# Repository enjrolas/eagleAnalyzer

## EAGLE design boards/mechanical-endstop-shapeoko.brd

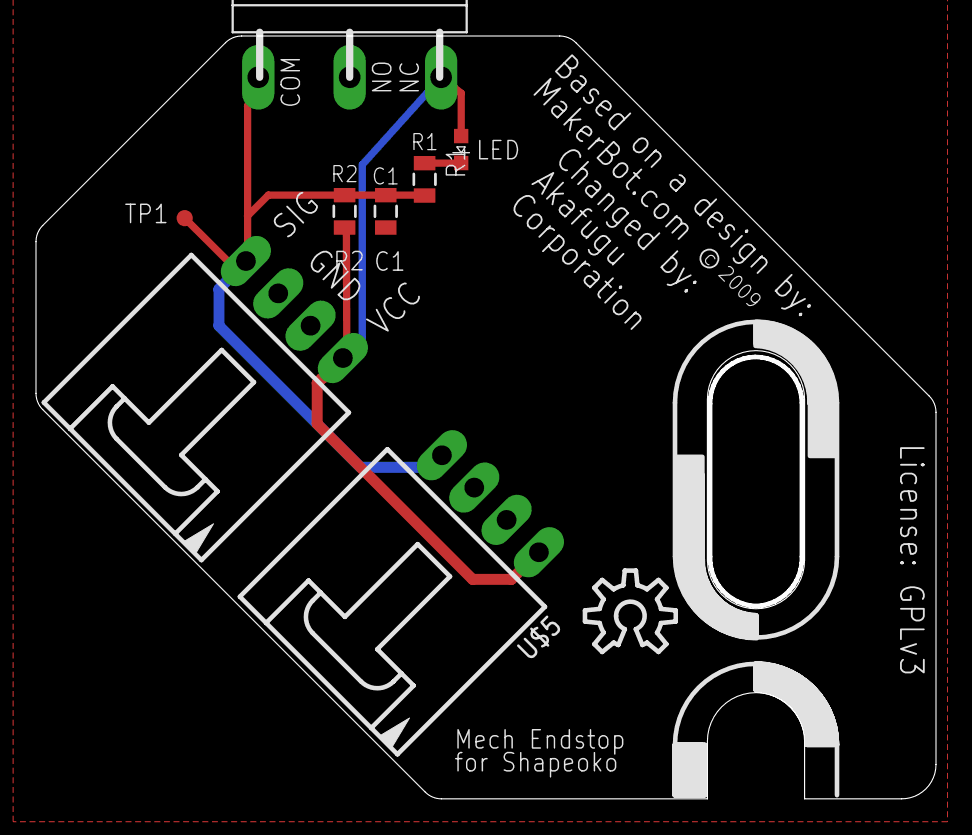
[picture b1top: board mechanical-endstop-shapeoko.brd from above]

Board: 2 copper layers, 50.0 x 42.4 mm, 9 parts (0 on the bottom side), 4 nets.

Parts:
C1: 0.1uF; 0805-CAP
DETECT: LED-0603
R1: 1K; R0805
R2: 10K; R0805
TP1: PTR1TP09R; TP09R
U$1, U$5: CDROM-HOR; 70553-04
U$2: OMRON-D2FA; OMRON-D2F-A
U$4: OSHW-LOGO-OUTLINE

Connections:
GND: C1.2, U$1.2, U$1.3, U$2.NO, U$5.2, U$5.3
unnamed: DETECT.C, R1.2
unnamed: C1.1, R1.1, R2.1, TP1.TP, U$1.4, U$2.COM, U$5.4
VCC: DETECT.A, R2.2, U$1.1, U$2.NC, U$5.1

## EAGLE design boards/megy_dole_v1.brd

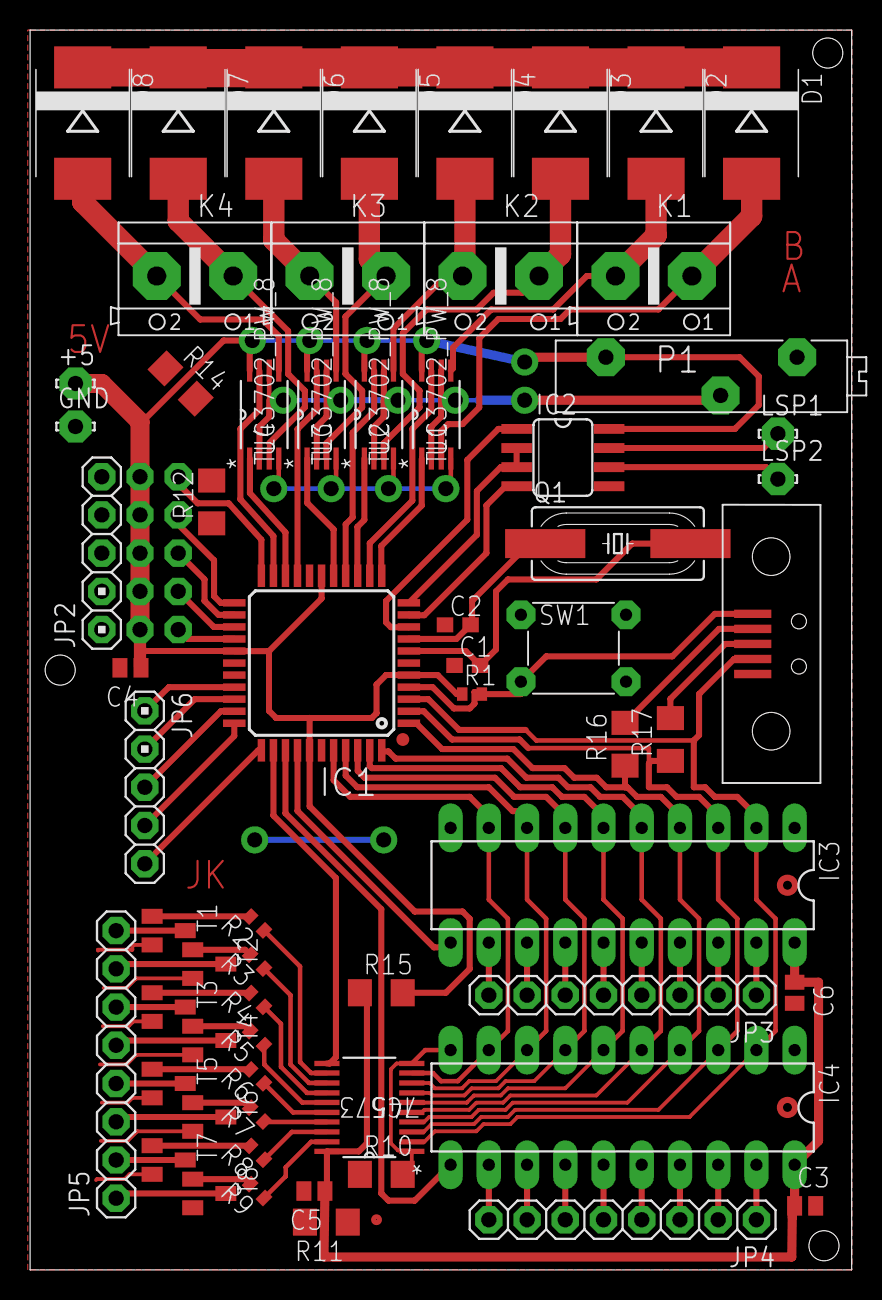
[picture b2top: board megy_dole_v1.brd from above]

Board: 2 copper layers, 54.6 x 82.4 mm, 65 parts (1 on the bottom side), 90 nets.

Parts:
+5: LSP10
C1, C2: C0603
C3, C4, C5, C6: 100n; C0504
D1: ES3D; SMC
D2, D3, D4, D5, D6, D7, D8: SMC
GND: LSP10
IC1: MEGA16-A; TQFP44
IC2: MAX485csa+; SO08
IC3, IC4: 74AC573N; DIL20
IC5: 74573; PW20
JP1: 2X05
JP2, JP6: 1X05
JP3, JP4, JP5: 1X08
K1, K2, K3, K4: ARK500/2
LSP1, LSP2: LSP10
P1: 10K; PM19
Q1: HC49UP
R1: 4K7; R0402
R2, R3, R4, R5, R6, R7, R8, R9: 220R; R0402
R10, R11, R12, R14, R15, R16, R17: R1206
SW1: P-B1720
T1, T2, T3, T4, T5, T6, T7, T8: BSS138; SOT23
U1, U2, U3, U4: TLC3702_PW_8; PW8
U$1: SEI-5

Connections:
GND: C1.1, C2.1, C3.2, C4.2, C5.2, C6.2, D1.C, D2.C, D3.C, D4.C, D5.C, D6.C, D7.C, D8.C, GND.MP, IC1.6, IC1.18, IC1.28, IC1.39, IC2.5, IC3.1, IC3.10, IC4.1, IC4.10, IC5.1, IC5.10, JP2.1, JP2.2, JP2.3, JP2.4, JP2.5, P1.B, R10.1, R10.2, R11.1, R11.2, R12.1, R12.2, R14.1, R14.2, SW1.2, T1.2, T2.2, T3.2, T4.2, T5.2, T6.2, T7.2, T8.2, U1.4, U2.4, U3.4, U4.4, U$1.P$5
MISO: IC1.2, IC3.3, IC4.3, IC5.3, R17.1
MOSI: IC1.1, IC3.4, IC4.4, IC5.4, R16.1
unnamed: IC1.10, IC2.4
unnamed: IC1.11, IC2.2, IC2.3
unnamed: IC2.7, LSP1.MP
unnamed: IC1.9, IC2.1
unnamed: IC1.37, IC3.11
unnamed: IC2.6, LSP2.MP
unnamed: C1.2, IC1.7, Q1.2
unnamed: C2.2, IC1.8, Q1.1
unnamed: IC1.26, JP1.9
unnamed: IC1.25, JP1.7
unnamed: IC1.24, JP1.5
unnamed: IC1.23, JP1.3
unnamed: IC1.22, JP1.1
unnamed: IC1.40, IC3.9, IC4.9, IC5.9
unnamed: IC1.41, IC3.8, IC4.8, IC5.8
unnamed: IC1.42, IC3.7, IC4.7, IC5.7
unnamed: IC1.12, U1.1
unnamed: IC1.13, U1.7
unnamed: IC1.20, U4.1
unnamed: D1.A, K1.1, U1.3
unnamed: D2.A, K1.2, U1.5
unnamed: IC1.43, IC3.6, IC4.6, IC5.6
unnamed: IC1.44, IC3.5, IC4.5, IC5.5
unnamed: IC1.21, U4.7
unnamed: D7.A, K4.1, U4.3
unnamed: D8.A, K4.2, U4.5
unnamed: P1.C, U1.2, U1.6, U2.2, U2.6, U3.2, U3.6, U4.2, U4.6
unnamed: IC1.14, U2.1
unnamed: IC1.15, U2.7
unnamed: D3.A, K2.1, U2.3
unnamed: D4.A, K2.2, U2.5
unnamed: IC1.16, U3.1
unnamed: IC1.19, U3.7
unnamed: D5.A, K3.1, U3.3
unnamed: D6.A, K3.2, U3.5
unnamed: R16.2, U$1.P$2
unnamed: R17.2, U$1.P$3
unnamed: IC4.19, JP4.1
unnamed: IC4.18, JP4.2
unnamed: IC4.17, JP4.3
unnamed: IC4.16, JP4.4
unnamed: IC3.19, JP3.1
unnamed: IC3.18, JP3.2
unnamed: IC3.17, JP3.3
unnamed: IC3.16, JP3.4
unnamed: IC3.15, JP3.5
unnamed: IC3.14, JP3.6
unnamed: IC3.13, JP3.7
unnamed: IC3.12, JP3.8
unnamed: IC4.15, JP4.5
unnamed: IC4.14, JP4.6
unnamed: IC4.13, JP4.7
unnamed: IC4.12, JP4.8
unnamed: IC1.36, IC4.11
unnamed: IC1.35, IC5.11
unnamed: IC5.12, R2.1
unnamed: R2.2, T1.1
unnamed: JP5.8, T1.3
unnamed: R3.2, T2.1
unnamed: IC5.13, R3.1
unnamed: JP5.7, T2.3
unnamed: IC5.19, R9.1
unnamed: R4.2, T3.1
unnamed: IC5.14, R4.1
unnamed: JP5.6, T3.3
unnamed: R5.2, T4.1
unnamed: R6.2, T5.1
unnamed: R7.2, T6.1
unnamed: R8.2, T7.1
unnamed: R9.2, T8.1
unnamed: JP5.5, T4.3
unnamed: JP5.4, T5.3
unnamed: JP5.3, T6.3
unnamed: JP5.2, T7.3
unnamed: JP5.1, T8.3
unnamed: IC5.18, R8.1
unnamed: IC5.17, R7.1
unnamed: IC5.16, R6.1
unnamed: IC5.15, R5.1
unnamed: IC1.30, JP6.1
unnamed: IC1.31, JP6.2
unnamed: IC1.32, JP6.3
unnamed: IC1.33, JP6.4
unnamed: IC1.34, JP6.5
RESET: IC1.4, R1.2, SW1.1, U$1.P$1
SCK: IC1.3, IC3.2, IC4.2, IC5.2, U$1.P$4
VCC: +5.MP, C3.1, C4.1, C5.1, C6.1, IC1.5, IC1.17, IC1.27, IC1.38, IC2.8, IC3.20, IC4.20, IC5.20, JP1.2, JP1.4, JP1.6, JP1.8, JP1.10, P1.A, R1.1, R15.1, R15.2, U1.8, U2.8, U3.8, U4.8

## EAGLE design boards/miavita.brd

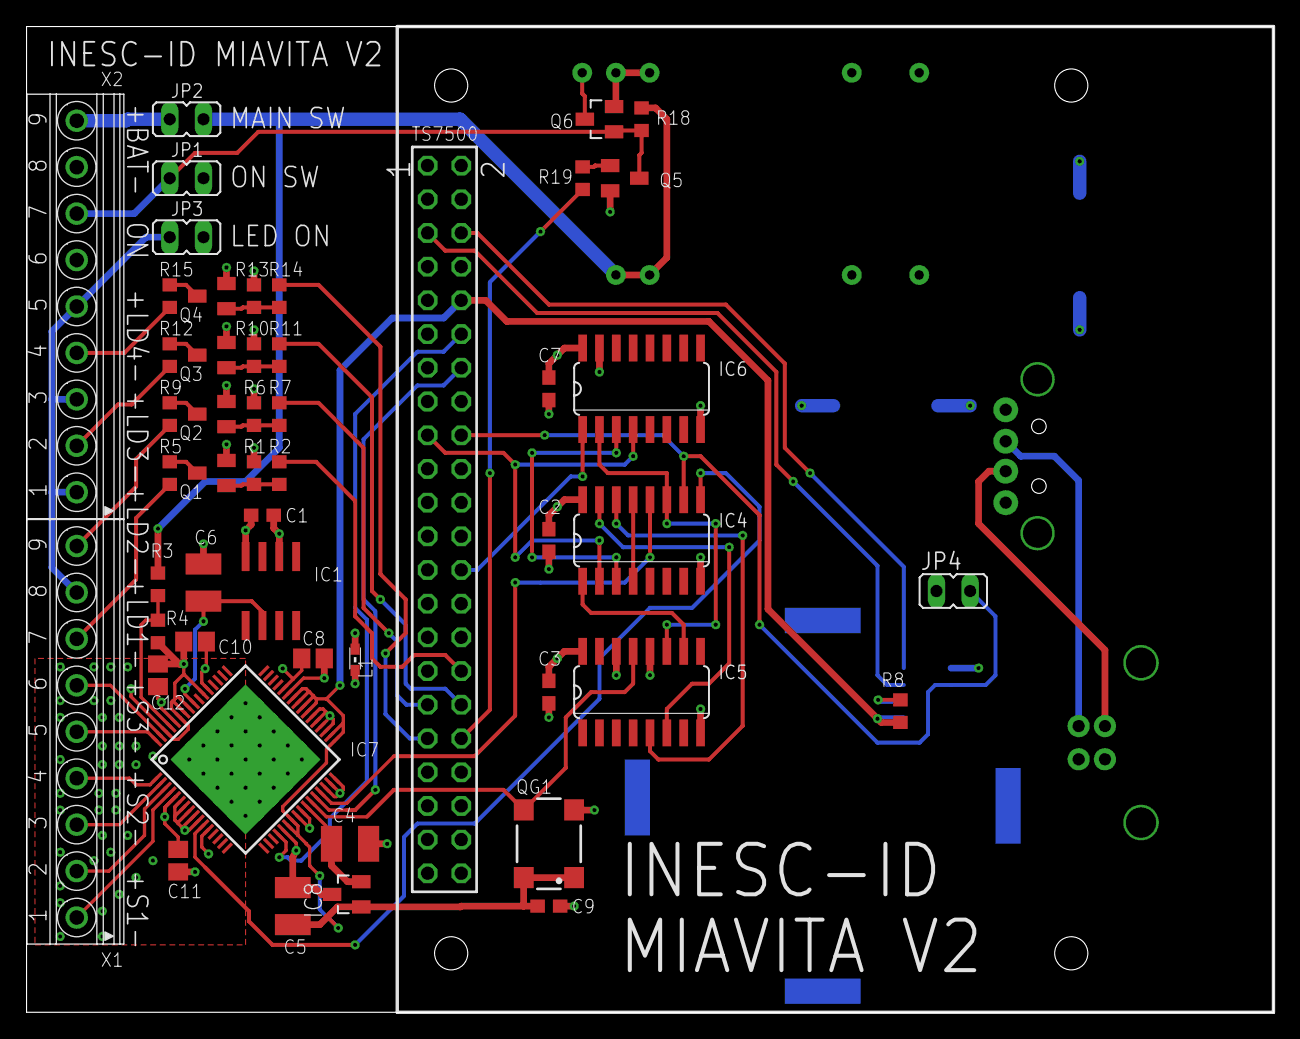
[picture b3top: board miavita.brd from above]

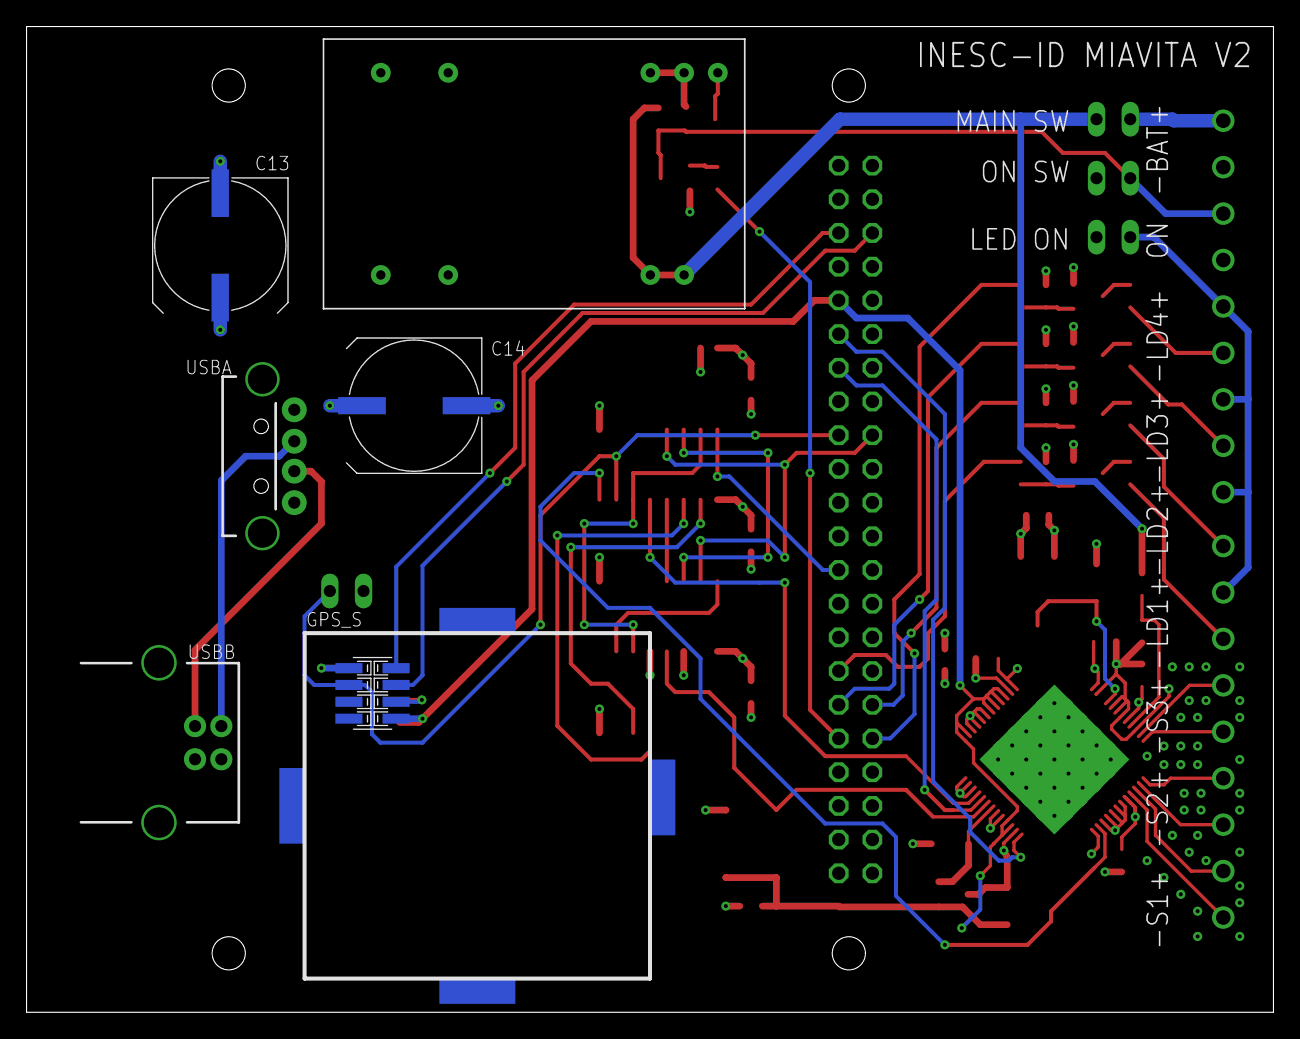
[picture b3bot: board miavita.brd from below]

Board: 4 copper layers, 94.0 x 74.3 mm, 56 parts (6 on the bottom side), 55 nets.

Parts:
C1: 1uF; C0603
C2, C3, C7: 100nF; C0603
C4, C5, C6: 10uF; C1210
C8, C10, C11, C12: 10uF; C0805
C9: 0.1uF; C0603
C13, C14: 220uF/35V; UD-10X10_NICHICON
GPS_S: 1296-T08; 1296-08
IC1: REF02D; SO08
IC4: 4572D; SO16
IC5: 74AC590D; SO16
IC6: 74LS157D; SO16
IC7: ADS1278; HTQFP-64-PAP
IC8: R3318AI; SOT23
JP1, JP2, JP3, JP4: JP1
L1: L0603
Q1, Q2, Q3, Q4, Q5: BC847B; SOT23
Q6: 2N7002CK; SOT23
QG1: SM77H
R1, R6, R10, R13, R18: 47K; R0603
R2, R7, R11, R14, R19: 10K; R0603
R3: 510k; R0603
R4, R8: 100k; R0603
R5, R9, R12, R15: 220R; R0603
TS7500: SSW-122-02-S-D
U1: TEN 8-1211; TRACOPOWER_TEN-8-SERIES
USBA: USB-A-H
USBB: USBPTH; USB-B-PTH
X1, X2: 1751316

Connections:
2.5V: C6.1, IC1.6, IC7.56
+1V8: C4.1, IC7.26, IC8.2
+3V3: C5.1, C9.1, GPS_S.8, IC7.22, IC7.23, IC7.33, IC7.34, IC7.39, IC7.40, IC7.41, IC7.42, IC8.1, QG1.1, QG1.4, R8.1, TS7500.10
+5V: C1.1, C2.1, C3.1, C7.1, C13.+, C14.+, IC1.2, IC4.16, IC5.16, IC6.16, JP3.2, L1.2, TS7500.15, U1.14, USBA.GND, X2.6
+12V: JP2.2, R3.2, R18.1, U1.22, U1.23
ADC_DATA: IC7.20, TS7500.12
CONT_144: IC4.3, IC6.3
CONT_RST: IC4.1, IC5.10
DR_INT: IC4.2, IC6.4, TS7500.17
FIRST_ADC_INT: IC4.11, IC5.11, IC6.2
GND: C1.2, C2.2, C3.2, C4.2, C5.2, C6.2, C7.2, C8.2, C9.2, C10.2, C11.2, C12.2, C13.-, C14.-, GPS_S.1, IC1.4, IC4.8, IC5.8, IC5.12, IC5.14, IC6.8, IC6.15, IC7.6, IC7.7, IC7.8, IC7.9, IC7.10, IC7.12, IC7.21, IC7.24, IC7.25, IC7.30, IC7.31, IC7.32, IC7.35, IC7.36, IC7.37, IC7.38, IC7.43, IC7.54, IC7.57, IC7.58, IC7.59, IC7.62, IC7.EXP1, IC7.EXP2, IC7.EXP3, IC7.EXP4, IC7.EXP5, IC7.EXP6, IC7.EXP7, IC7.EXP8, IC7.EXP9, IC7.EXP10, IC7.EXP11, IC7.EXP12, IC7.EXP13, IC7.EXP14, IC7.EXP15, IC7.EXP16, IC7.EXP17, IC7.EXP18, IC7.EXP19, IC7.EXP20, IC7.EXP21, IC7.EXP22, IC7.EXP23, IC7.EXP24, IC7.EXP25, IC8.3, JP1.1, JP4.1, Q1.2, Q2.2, Q3.2, Q4.2, Q5.2, Q6.2, QG1.2, R1.2, R4.2, R6.2, R10.2, R13.2, TS7500.7, TS7500.16, U1.2, U1.3, U1.16, USBA.VBUS, USBB.GND, X2.8
GPS_PPS: GPS_S.3, IC4.10, JP4.2, TS7500.18
LED1: R2.1, TS7500.32
LED2: R7.1, TS7500.33
LED3: R11.1, TS7500.34
LED4: R14.1, TS7500.35
unnamed: IC6.1, TS7500.26
unnamed: IC4.15, IC5.6
unnamed: IC4.14, IC5.5
unnamed: IC4.9, IC7.11
unnamed: IC4.4, IC4.13
unnamed: IC4.12, IC7.29
unnamed: IC7.3, X1.2
unnamed: Q5.1, R19.2
unnamed: IC7.4, X1.1
unnamed: IC7.1, X1.4
unnamed: IC7.61, R3.1, R4.1
unnamed: USBA.D+, USBB.D-
unnamed: IC7.63, X1.6
unnamed: Q2.1, R6.1, R7.2
unnamed: Q2.3, R9.1
unnamed: IC5.13, IC7.27, QG1.3
unnamed: USBA.D-, USBB.D+
unnamed: C8.1, C10.1, C11.1, C12.1, IC7.5, IC7.44, IC7.53, IC7.60, L1.1
unnamed: R9.2, X1.9
unnamed: Q3.1, R10.1, R11.2
unnamed: Q3.3, R12.1
unnamed: R12.2, X2.2
unnamed: Q4.1, R13.1, R14.2
unnamed: Q4.3, R15.1
unnamed: R15.2, X2.4
unnamed: JP2.1, X2.9
unnamed: JP3.1, X1.8, X2.1, X2.3, X2.5
unnamed: IC7.2, X1.3
unnamed: JP1.2, Q5.3, Q6.1, R18.2, X2.7
unnamed: Q6.3, U1.1
unnamed: IC7.64, X1.5
unnamed: Q1.3, R5.1
unnamed: Q1.1, R1.1, R2.2
unnamed: R5.2, X1.7
unnamed: GPS_S.2, TS7500.6
unnamed: GPS_S.4, TS7500.5
unnamed: GPS_S.6, R8.2
ON: R19.1, TS7500.36
SPI_CLOCK: IC7.28, TS7500.14

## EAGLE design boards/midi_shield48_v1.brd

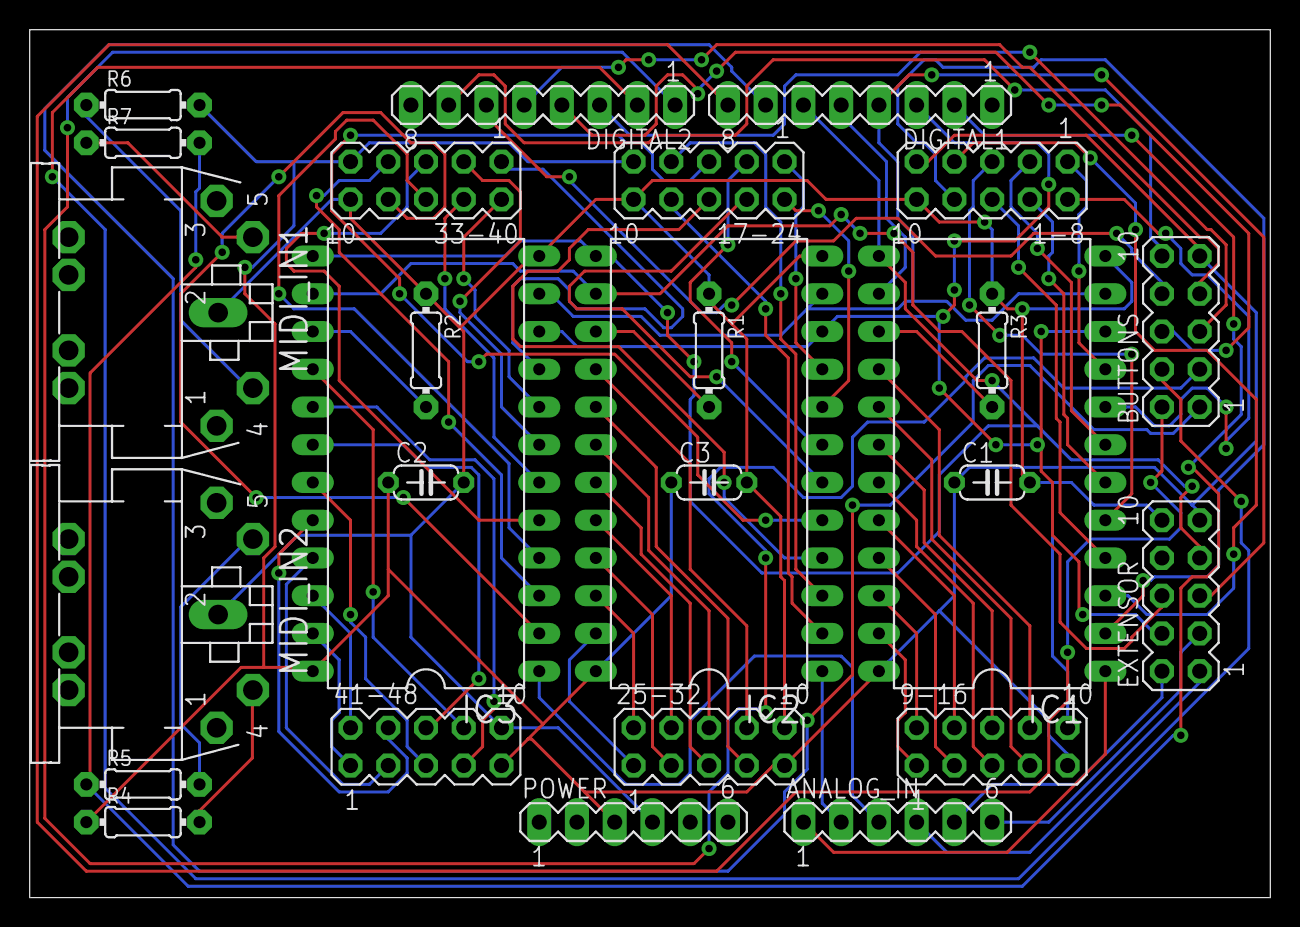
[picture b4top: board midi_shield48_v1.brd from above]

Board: 2 copper layers, 83.5 x 58.4 mm, 27 parts (0 on the bottom side), 77 nets.

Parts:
1-8, 9-16, 17-24, 25-32, 33-40, 41-48: MA05-2
ANALOG_IN: MA06-1
BUTTONS: MA05-2
C1, C2, C3: 0.1uF; C050-024X044
DIGITAL1, DIGITAL2: MA08-1
EXTENSOR: MA05-2
IC1, IC2, IC3: 4067N; DIL24-6
MIDI_IN1, MIDI_IN2: MIDIJACK; CP-2350
POWER: MA06-1
R1, R2, R3: 10k; 0204/7
R4, R5, R6, R7: 220; 0204/7

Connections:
ACOMM1: ANALOG_IN.1, IC1.1
ACOMM2: ANALOG_IN.2, IC2.1
ACOMM3: ANALOG_IN.3, IC3.1
ACOMM4: ANALOG_IN.4, EXTENSOR.1
ACOMM5: ANALOG_IN.5, EXTENSOR.2
ACOMM6: ANALOG_IN.6, EXTENSOR.3
BUTTON1: BUTTONS.1, DIGITAL1.7
BUTTON2: BUTTONS.2, DIGITAL1.8
BUTTON3: BUTTONS.3, DIGITAL2.1
BUTTON4: BUTTONS.4, DIGITAL2.2
DIGITAL_GND: BUTTONS.10, DIGITAL2.7
GND: 1-8.10, 9-16.10, 17-24.10, 25-32.10, 33-40.10, 41-48.10, C1.2, C2.2, C3.2, EXTENSOR.10, IC1.12, IC2.12, IC3.12, MIDI_IN1.2, MIDI_IN2.2, POWER.4, R1.1, R2.1, R3.1
LED1: BUTTONS.5, DIGITAL2.3
LED2: BUTTONS.6, DIGITAL2.4
LED3: BUTTONS.7, DIGITAL2.5
LED4: BUTTONS.8, DIGITAL2.6
M1P1: 1-8.1, IC1.9
M1P2: 1-8.2, IC1.8
M1P3: 1-8.3, IC1.7
M1P4: 1-8.4, IC1.6
M1P5: 1-8.5, IC1.5
M1P6: 1-8.6, IC1.4
M1P7: 1-8.7, IC1.3
M1P8: 1-8.8, IC1.2
M1P9: 9-16.1, IC1.23
M1P10: 9-16.2, IC1.22
M1P11: 9-16.3, IC1.21
M1P12: 9-16.4, IC1.20
M1P13: 9-16.5, IC1.19
M1P14: 9-16.6, IC1.18
M1P15: 9-16.7, IC1.17
M1P16: 9-16.8, IC1.16
M2P1: 17-24.1, IC2.9
M2P2: 17-24.2, IC2.8
M2P3: 17-24.3, IC2.7
M2P4: 17-24.4, IC2.6
M2P5: 17-24.5, IC2.5
M2P6: 17-24.6, IC2.4
M2P7: 17-24.7, IC2.3
M2P8: 17-24.8, IC2.2
M2P9: 25-32.1, IC2.23
M2P10: 25-32.2, IC2.22
M2P11: 25-32.3, IC2.21
M2P12: 25-32.4, IC2.20
M2P13: 25-32.5, IC2.19
M2P14: 25-32.6, IC2.18
M2P15: 25-32.7, IC2.17
M2P16: 25-32.8, IC2.16
M3P1: 33-40.1, IC3.9
M3P2: 33-40.2, IC3.8
M3P3: 33-40.3, IC3.7
M3P4: 33-40.4, IC3.6
M3P5: 33-40.5, IC3.5
M3P6: 33-40.6, IC3.4
M3P7: 33-40.7, IC3.3
M3P8: 33-40.8, IC3.2
M3P9: 41-48.1, IC3.23
M3P10: 41-48.2, IC3.22
M3P11: 41-48.3, IC3.21
M3P12: 41-48.4, IC3.20
M3P13: 41-48.5, IC3.19
M3P14: 41-48.6, IC3.18
M3P15: 41-48.7, IC3.17
M3P16: 41-48.8, IC3.16
MIDITX: DIGITAL1.2, R5.1, R7.2
unnamed: IC1.15, R3.2
unnamed: IC2.15, R1.2
unnamed: IC3.15, R2.2
unnamed: MIDI_IN2.5, R5.2
unnamed: MIDI_IN2.4, R4.2
unnamed: MIDI_IN1.5, R7.1
unnamed: MIDI_IN1.4, R6.1
S0: DIGITAL1.3, EXTENSOR.4, IC1.10, IC2.10, IC3.10
S1: DIGITAL1.4, EXTENSOR.5, IC1.11, IC2.11, IC3.11
S2: DIGITAL1.5, EXTENSOR.6, IC1.14, IC2.14, IC3.14
S3: DIGITAL1.6, EXTENSOR.7, IC1.13, IC2.13, IC3.13
VCC: 1-8.9, 9-16.9, 17-24.9, 25-32.9, 33-40.9, 41-48.9, BUTTONS.9, C1.1, C2.1, C3.1, EXTENSOR.9, IC1.24, IC2.24, IC3.24, POWER.3, R4.1, R6.2

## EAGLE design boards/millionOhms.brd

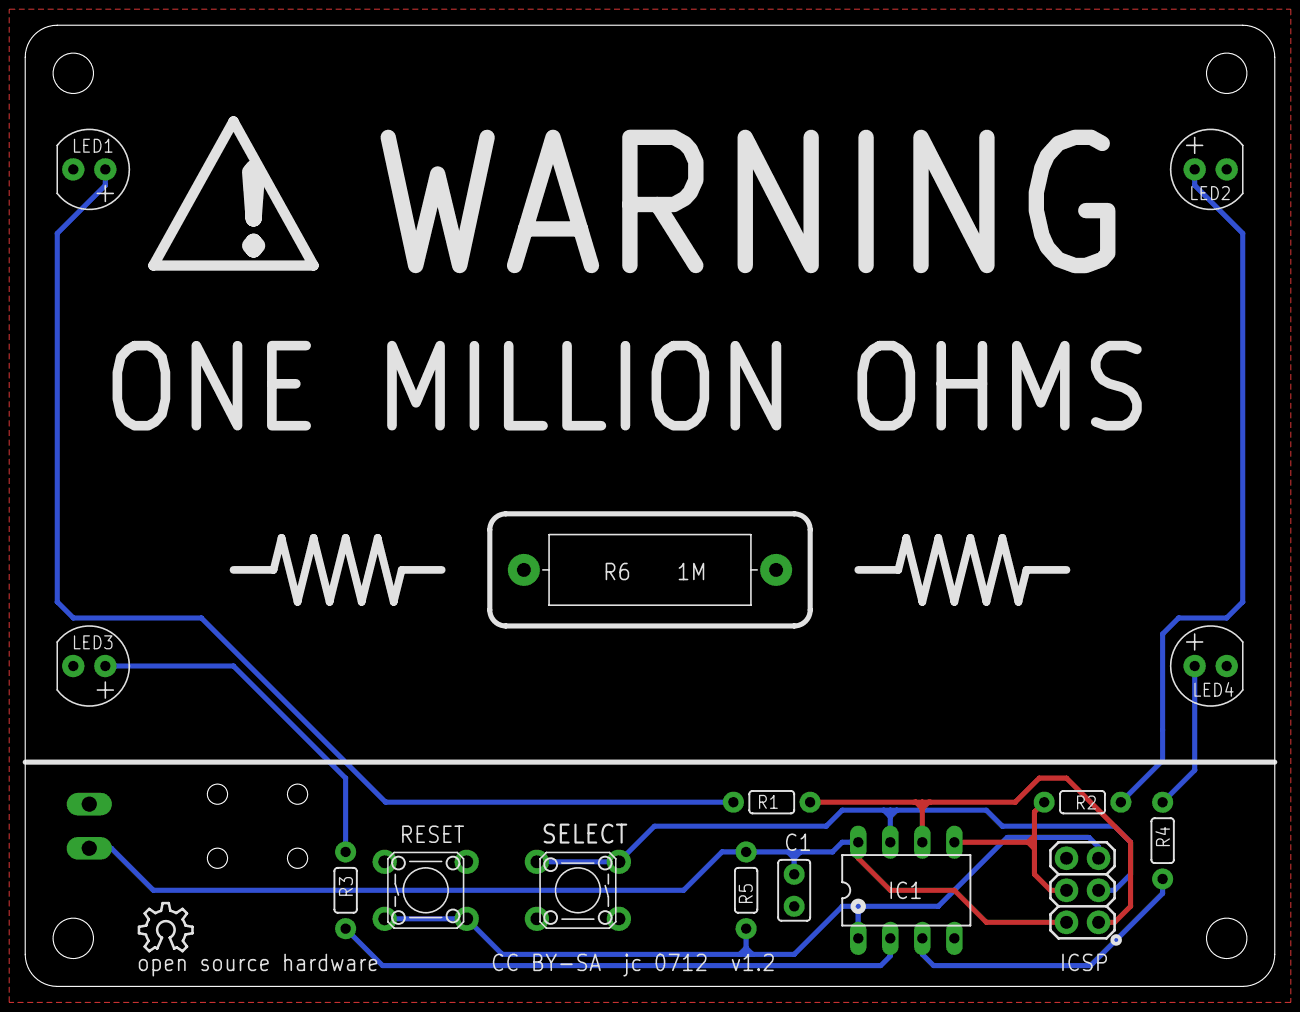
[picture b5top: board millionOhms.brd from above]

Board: 2 copper layers, 99.1 x 76.2 mm, 17 parts (1 on the bottom side), 12 nets.

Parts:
C1: 2.2uF; C025-025X050
IC1: ATtiny85V-10PU; DIL08
J1: ICSP; 2X3
LED1, LED2, LED3, LED4: 5mm; LED5MM
LOGO2: OSHW_LOGO_8MILX0150-NT; OSHW_8X150_NOTEXT
R1, R2, R3, R4: 100; 0204/6
R5: 10K; 0204/6
R6: 1M; 5616/20
S1: SELECT; B3F-10XXOCT
S2: RESET; B3F-10XXOCT
TB1: +3VDC-; OST-TB-2-3.5MM

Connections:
GND: C1.2, IC1.4, J1.6, LED1.K, LED2.K, LED3.K, LED4.K, S1.1, S1.2, S2.1, S2.2, TB1.P$2
MISO: IC1.6, J1.1, R1.2
MOSI: IC1.5, J1.4, R2.2
unnamed: LED2.A, R2.1
unnamed: LED1.A, R1.1
unnamed: LED3.A, R3.1
unnamed: LED4.A, R4.1
unnamed: IC1.2, R3.2
unnamed: IC1.3, R4.2
RESET: IC1.1, J1.5, R5.1, S2.3, S2.4
SCK: IC1.7, J1.3, S1.3, S1.4
VCC: C1.1, IC1.8, J1.2, R5.2, TB1.P$1

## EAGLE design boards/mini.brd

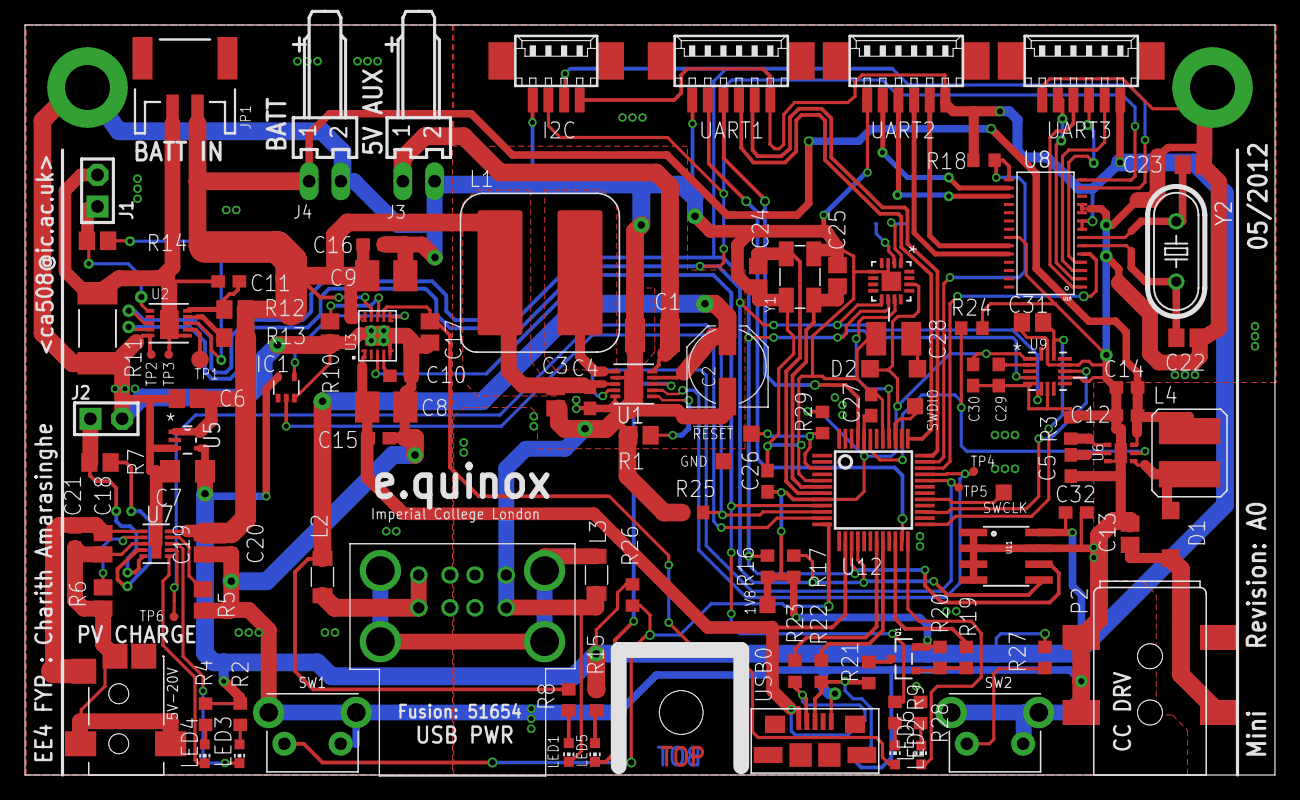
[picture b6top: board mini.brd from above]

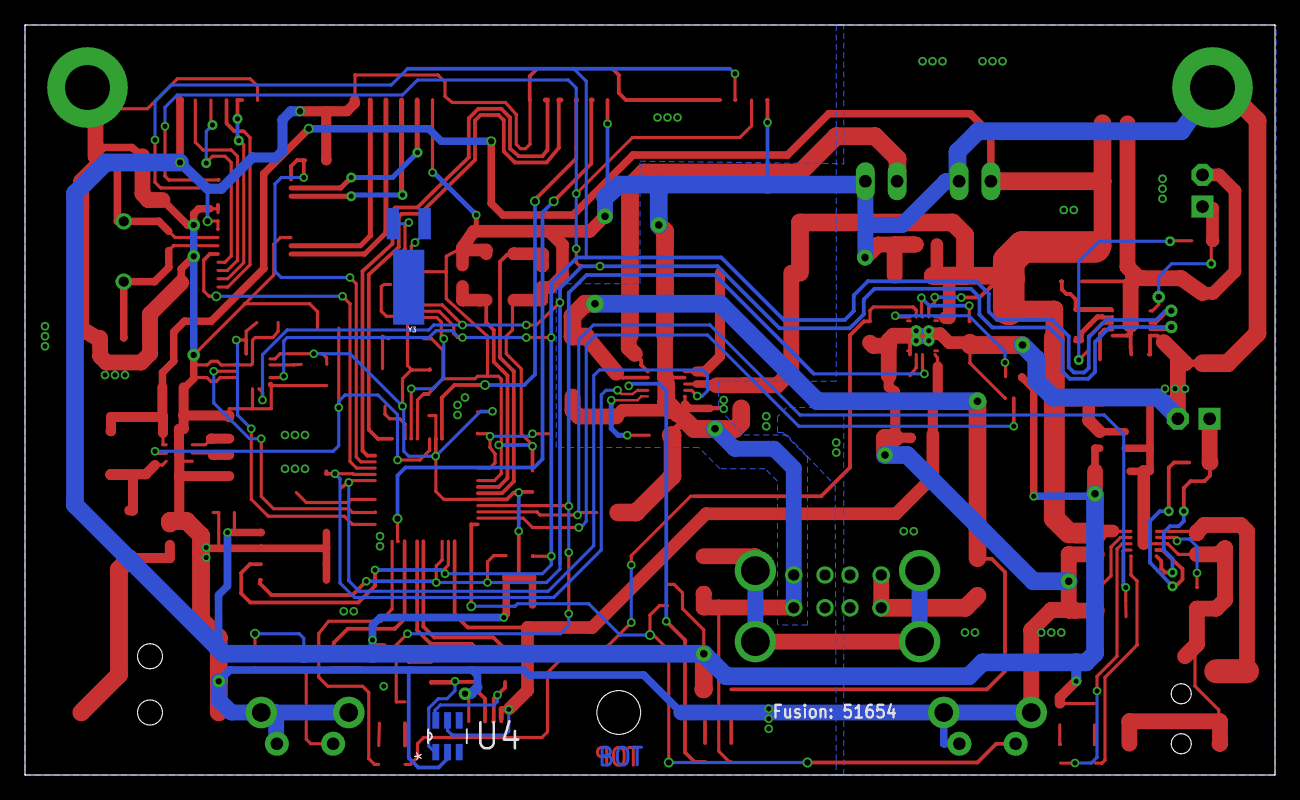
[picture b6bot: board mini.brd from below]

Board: 2 copper layers, 100.0 x 60.0 mm, 116 parts (2 on the bottom side), 84 nets.

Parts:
1V8: TPSTP13SQ; TP13SQ
!RESET!: TPSTP13SQ; TP13SQ
C1: 22uF; C1210
C2: 150uF; PANASONIC_D
C3: 10uF; C0805
C4, C14, C29, C30, C32: 0.1uF; C0603
C5: 220nF; C0603
C6: 100nF; C0805
C7: 1uF; C1206
C8, C9: 10uF; B/3528-21R
C10: 1n; C0603
C11: 10n; C0603
C12: 1uF; C0603
C13, C17, C18, C19: 1uF; C0805
C15, C16, C20, C21, C26, C27: 100n; C0603
C22, C23, C24, C25: C0805
C28: 0.015F; C3225
C31: 4.7uF; C0805
D1: MBR0540T1; SOD123
D2: SOD123
GND: TPSTP13SQ; TP13SQ
I2C: 53261-04
IC1: 74LVC1G06DCK; SC70-5
J1, J2: F-1X02-SIP-100-40; SIP-100-02-40
J3, J4: 22-05-7028-02; 7395-02
JP1: JST-2-SMD
L1: 2.2uH; SDR1006
L2, L3: 30ohm; L3216C
L4: 22uH; VLCF-SERIES
LED1: USB_ON; CHIP-LED0603
LED2: USB_CHG_GD; CHIP-LED0603
LED3: CHG; CHIP-LED0603
LED4: PG; CHIP-LED0603
LED5: USB_FAULT; CHIP-LED0603
LED6: USRLED; CHIP-LED0603
P1: CLIFF_DCJACK1.3MM; FC68145S
P2: CLIFF_DCJACK2.1-2.5MM; FC6814XS
Q1: MMBT2907; SOT23-R
R1: 28.7k; R0805
R2, R4, R15: 100; R0603
R3: 2.7; R0603
R5: RDPM; R0805
R6: 800; R0805
R7: RVTSB; R0805
R8: 1K; R0603
R9: 200; R0603
R10: 80k; R0805
R11: 0.015; R2512
R12: 150; R0805
R13: 1K; R0805
R14: 10K; R0805
R16, R17, R24, R26, R27, R29: 2.7k; R0603
R18: 1.5k; R0603
R19: 2K; R0603
R20, R25: 10K; R0603
R21: 1.5K; R0603
R22, R23: 33; R0603
R28: 500; R0603
SW1, SW2: B3F-3152; B3F-315X
SWCLK: TPSTP13SQ; TP13SQ
SWDIO: TPSTP13SQ; TP13SQ
TP1: TPTP14R; TP14R
TP2, TP3, TP4, TP5, TP6: TPTP07R; TP07R
U1: TPS2500; SON50P300X300X100-11N
U2: DS2786G+; DFN300X300X80-11N
U3: ISL9203; INTERSIL_DFN_3X3
U4: IP4220CZ6; SOT95P275X110-6N
U5: NCP4588DSQ25T1G; SOT65P210X110-5N
U6: TPS61160ADRVT; SON65P210X210X80-7N
U7: BQ24210DQCT; SON50P200X300X80-11N
U8: M41T62Q6F; QFN50P300X300X100-17N
U9: MMA8453Q; QFN50P300X300X100-16N
U10: SC16IS752; TSSOP28
U11: EEPROM-I2CSMD; SO08
U12: LPC11U24FBD48/401; LQFP48
UART1, UART2, UART3: 53261-06
USB0: TE1981584-1; TE-MICROUSB-AB
USB2: MULTICOMP-MC32594; MC32594
Y1: TXC-7B
Y2: 1.8432M; HC49U-V
Y3: 32.768kHz; CRYSTAL-32KHZ-SMD

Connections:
1.8V: 1V8.TP, C7.1, C26.1, C27.1, C30.1, C32.1, D2.A, I2C.1, IC1.5, Q1.2, R2.2, R4.2, R15.2, R16.2, R17.2, R18.2, R20.2, R26.2, R27.2, R29.2, U5.4, U8.14, U9.1, U10.8, U10.9, U11.8, U12.8, U12.44, UART1.1, UART2.1, UART3.1
!CHRG_ST!: R9.1, U3.P3, U12.9
!EN_PVCHG!: R25.2, TP6.TP, U7.7, U12.10
!EXT_UART_RST!: U10.5, U12.34
!USB_CHG_EN!: IC1.2, U12.11
+5V: C8.+, C15.1, U3.P1, U4.5, U12.14, USB0.P1
+5V/1: C2.+, L2.2, R8.2, U1.9
+5V/2: C1.1, J3.1, U1.10
+12V: C13.1, D1.C, P2.3
+18V: C18.1, C21.1, P1.3, U7.1
AXM_INT: U9.11, U12.27
AXM_ON: C31.1, U9.14, U12.25
CHRG_EN: IC1.4, U3.P6
EN_5V: TP5.TP, U1.4, U12.32
EN_USB: TP4.TP, U1.7, U12.33
EXT_UART_IRQ: R18.1, U10.15, U12.35
FG_AIN0: J1.1, R14.1, U2.1
FG_VOUT: R14.2, U2.8
GND: C1.2, C2.-, C3.1, C4.2, C5.2, C6.2, C7.2, C8.-, C9.-, C10.2, C12.2, C13.2, C14.2, C15.2, C16.2, C17.2, C18.2, C19.2, C20.2, C21.2, C22.1, C23.1, C24.1, C25.1, C26.2, C27.2, C28.2, C29.2, C30.2, C31.2, C32.2, GND.TP, I2C.4, IC1.3, J2.2, J3.2, J4.2, L3.2, LED1.C, P1.1, P1.4A, P1.4B, P2.1A, P2.1B, R1.1, R3.1, R5.1, R6.1, R10.1, R11.2, R24.1, R25.1, R28.1, SW1.2, SW1.3, SW1.4, SW2.2, SW2.3, SW2.4, TP2.TP, U1.2, U1.5, U1.11, U2.5, U3.P5, U3.P$1, U3.P$2, U3.P$3, U3.P$4, U3.PAD, U4.2, U5.3, U6.3, U6.7, U7.3, U7.11, U8.3, U8.5, U8.17, U9.5, U9.7, U9.10, U9.12, U9.15, U10.10, U10.11, U10.22, U11.1, U11.2, U11.3, U11.4, U11.7, U12.5, U12.41, UART1.6, UART2.6, UART3.6, USB0.P5, USB2.USB1-4, USB2.USB2-4, Y1.2, Y1.4
GNDA: C11.2, J1.2, JP1.1, R11.1, TP3.TP, U2.6, U2.11
LED_DIM: R24.2, U6.5, U12.43
MCU_USB_DN: R23.2, U12.19
MCU_USB_DP: R22.2, U12.20
unnamed: L1.P$2, U1.1
unnamed: C11.1, R12.1, U2.10
unnamed: R10.2, U3.P8
unnamed: L2.1, USB2.USB1-1, USB2.USB2-1
unnamed: C10.1, U3.P4
unnamed: L3.1, USB2.P$1, USB2.P$2, USB2.P$3, USB2.P$4
unnamed: LED1.A, R8.1
unnamed: R13.1, U2.9
unnamed: LED2.C, R9.2
unnamed: R1.2, U1.6
unnamed: D1.A, L4.1, U6.4
unnamed: C17.1, LED2.A, U3.P7
unnamed: C5.1, U6.2
unnamed: R3.2, U6.1
unnamed: R7.2, U7.4
unnamed: C28.1, D2.C
unnamed: R5.2, U7.9
unnamed: R6.2, U7.2
unnamed: LED5.A, R15.1
unnamed: LED4.A, R4.1
unnamed: LED3.A, R2.1
unnamed: Q1.1, R19.2, R20.1
unnamed: C22.2, U10.6, Y2.2
unnamed: R27.1, SW2.1
unnamed: C24.2, U12.7, Y1.3
unnamed: C25.2, U12.6, Y1.1
unnamed: LED6.C, R28.2
unnamed: U10.3, UART3.2
unnamed: C23.2, U10.7, Y2.1
unnamed: U10.4, UART3.3
unnamed: U10.23, UART2.2
unnamed: U10.24, UART2.3
unnamed: U10.17, UART2.4
unnamed: U10.16, UART2.5
unnamed: U10.2, UART3.5
unnamed: U10.1, UART3.4
unnamed: U12.36, UART1.2
unnamed: U12.37, UART1.3
unnamed: U12.45, UART1.4
unnamed: U12.23, UART1.5
unnamed: U8.2, Y3.X1
unnamed: Q1.3, R21.2
unnamed: U8.1, Y3.X2
unnamed: !RESET!.TP, R29.1, U12.3
unnamed: C29.1, U9.2
PVCHG_TS: J2.1, R7.1, U7.5
PV_CHG: LED3.C, U7.8
PV_PG: LED4.C, U7.6
RTC_ALARM: U8.11, U12.40
SCL: I2C.2, R16.1, U2.3, U8.10, U9.4, U10.13, U11.6, U12.15
SDA: I2C.3, R17.1, U2.4, U8.9, U9.6, U10.14, U11.5, U12.16
SW1: R26.1, SW1.1, U12.12
SWCLK: SWCLK.TP, U12.29
SWDIO: SWDIO.TP, U12.39
USB_CONNECT: R19.1, U12.22
USB_DM: R23.1, U4.6, USB0.P2
USB_DP: R21.1, R22.1, U4.1, USB0.P3
USB_FAULT: LED5.C, U1.8
USRLED: LED6.A, U12.24
VBAT: C3.2, C4.1, C6.1, C9.+, C12.1, C14.1, C16.1, C19.1, C20.1, J4.1, JP1.2, L1.P$1, L4.2, R12.2, R13.2, U1.3, U3.P9, U3.P10, U5.1, U5.5, U6.6, U7.10
VPROG: TP1.TP, U2.7

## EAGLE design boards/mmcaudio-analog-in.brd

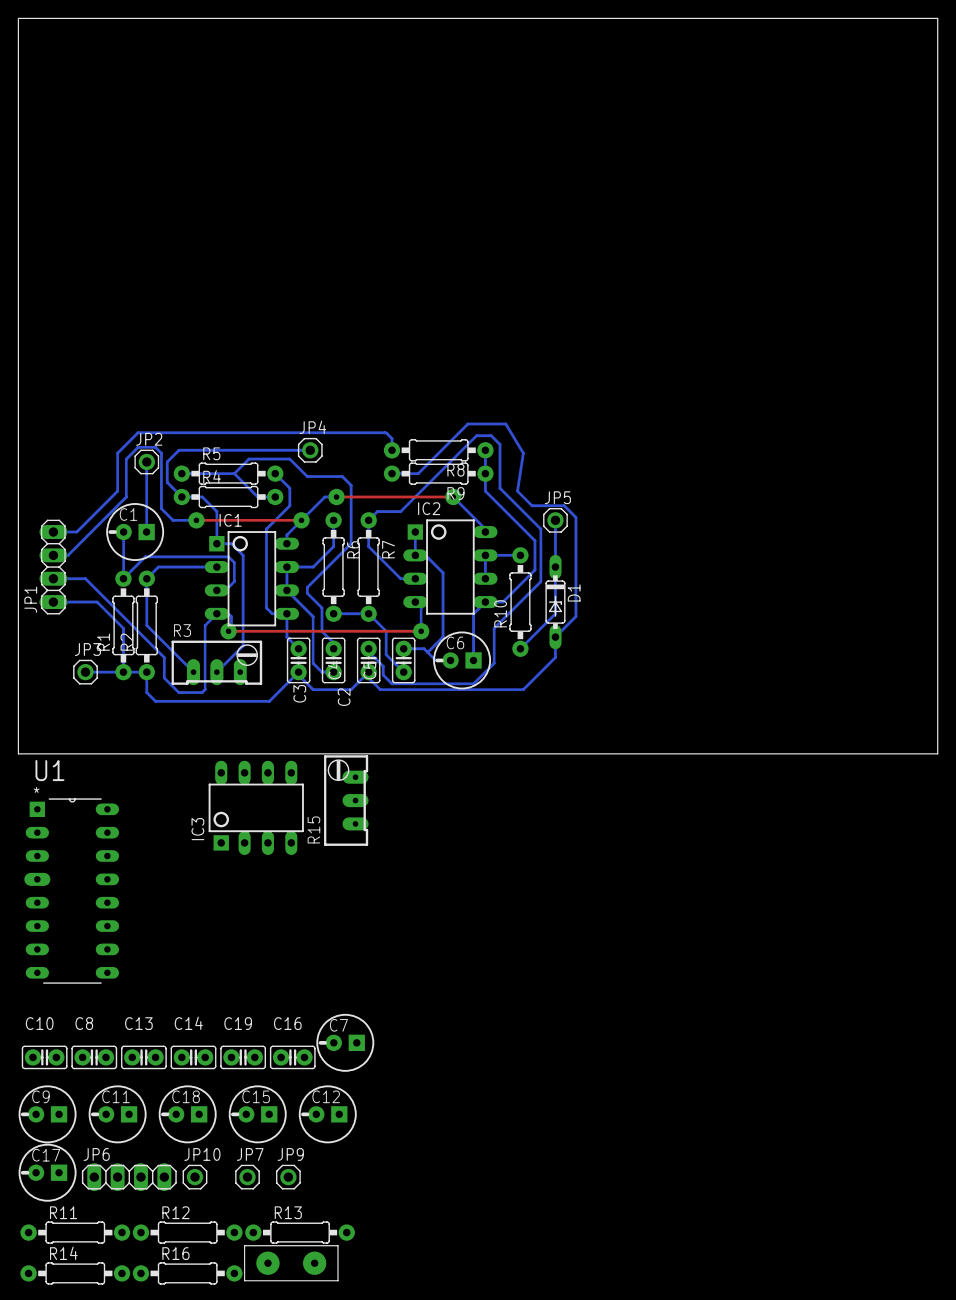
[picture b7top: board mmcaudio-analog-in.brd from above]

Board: 2 copper layers, 100.0 x 80.0 mm, 50 parts (0 on the bottom side), 35 nets.

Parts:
C1, C6: 10uF; POL-CAP-COMMON
C2, C5, C8, C14: 223; C025-060X050
C3, C10, C13: 222; C025-060X050
C4: 103; C025-060X050
C7, C9, C11, C12, C15, C18: 100uF; POL-CAP-COMMON
C16, C19: 104; C025-060X050
C17: POL-CAP-COMMON
D1: Z-5V1; DO35Z7
IC1, IC2, IC3: TL082; DIP08
JP1, JP6: 1X04
JP2, JP3, JP4, JP5, JP7, JP9, JP10: 1X01
JP8: SPEAKER; 1X02/0.5"
R1, R2, R10: 1k; R-US-COMMON
R3: 100k; RTRIM-COMMON
R4, R11: 6.8k; R-US-COMMON
R5, R12: 27k; R-US-COMMON
R6, R7: 3.3k; R-US-COMMON
R8, R9, R16: 10k; R-US-COMMON
R13, R14: 1.5k; R-US-COMMON
R15: 10k; RTRIM-COMMON
U1: TEA2025B; DIP254P762X510-16

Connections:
+12V: C7.+, IC1.8, IC2.8, IC3.4, JP1.3, JP6.3, U1.16
-12V: IC1.4, IC2.4, IC3.8, JP1.2, JP6.2
GND: C3.1, C4.1, C7.-, C9.-, C10.1, C12.-, C13.1, C16.1, C19.1, D1.A, JP1.1, JP3.1, JP6.1, JP10.1, R1.1, R2.1, R9.2, R16.2, U1.4, U1.5, U1.7, U1.9, U1.12, U1.13
unnamed: C1.-, IC1.3, R1.2
unnamed: IC1.2, R2.2, R3.1
unnamed: IC1.1, JP4.1, R3.2, R4.1
unnamed: C2.1, R4.2, R5.1
unnamed: C3.2, IC1.5, R5.2
unnamed: C2.2, IC1.6, IC1.7, R6.1
unnamed: C5.1, R6.2, R7.2
unnamed: C4.2, IC2.3, R7.1
unnamed: C5.2, C6.-, IC2.1, IC2.2
unnamed: C6.+, IC2.5, R8.1, R9.1
unnamed: IC2.6, IC2.7, R10.2
unnamed: D1.C, JP5.1, R10.1
unnamed: C1.+, JP2.1
unnamed: C8.1, R11.2, R12.1
unnamed: C10.2, IC3.3, R12.2
unnamed: C8.2, IC3.1, IC3.2, R13.1
unnamed: C14.1, R13.2, R14.2
unnamed: C13.2, IC3.6, R14.1
unnamed: C14.2, C17.+, IC3.5, IC3.7
unnamed: JP7.1, R11.1
unnamed: C17.-, JP9.1, R15.3
unnamed: C9.+, U1.11
unnamed: C11.+, U1.6
unnamed: C11.-, U1.1
unnamed: C18.-, C19.2, JP8.1, U1.15
unnamed: C18.+, U1.14
unnamed: C15.-, C16.2, JP8.2, U1.2
unnamed: C15.+, U1.3
unnamed: C12.+, U1.8
unnamed: R15.1, R16.1
PWR_AMP: R15.2, U1.10
VCC: JP1.4, JP6.4, R8.2

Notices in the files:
boards/mechanical-endstop-shapeoko.brd:
License: GPLv3
boards/millionOhms.brd:
CC BY-SA  jc 0712  v1.2
Licensed under the Creative Commons Attribution-ShareAlike 3.0
unported license, http://creativecommons.org/licenses/by-sa/3.0
parts and their libraries:
Copyright (C) PaJa 2011
Copyright (C) PaJa 2001-2011
con-headers-jp: Copyright (C) 2008, Bob Starr
SparkFun-Connectors: Licensing: CC v3.0 Share-Alike You are welcome to use this library for commercial purposes.
